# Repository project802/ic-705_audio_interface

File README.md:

# IC-705 Audio Interface

This project was done as a learning exercise for me, and a way to have some fun. I wanted to use my IC-705 with just an iPhone to drive digital mode communications, but limitations of both the radio and the phone meant things like straight USB or Bluetooth wouldn't work. There is a solution path with WiFi-based software or a Digirig, but I didn't want to be locked into a single app (even though I use it on my iPad and find it very good) or buy hardware when I thought I could make something myself and learn.

The result is a minimal solution that is ideal for remote or portable operation (such as POTA or SOTA) with iOS.

All said and done, I have got this working with iFTx and Greyline FT8 to successfully complete QSOs!

In the end, this device is just an audio level shifter with isolation. It can be used with any device (PC, tablet, phone) that has an analog audio input (microphone or line in) and an analog audio output. Just tune the trim pots to hit the voltage levels you need.

Have a PC? Just use the built-in USB functionality or Wi-Fi interface. This adds no value, whatsoever, over those options. This is really for phones using inexpensive (or free) apps that require VOX activation.

## (Non-)Solution Problem Space

### USB Cable or Bluetooth

The radio presents a BT/USB interface to the iOS device, but there are two issues that prevent this from working:
- iOS does not allow for serial port interfaces over USB or BT so an app can't control PTT via the CAT interface. Even with serial port support, this may reduce the number of app choices to ones that specifically support CAT.
- IC-705 doesn't do VOX over USB or BT so we can't just send audio. Icom...come on! The firmware for this is *so tiny*!

There are also reports that the IC-705 has poor RFI rejection via USB so depending on what is plugged in, this could make digital mode operation difficult.

You can theoretically make these interfaces work if you manually activate PTT. That doesn't sound fun.

### Digirig

This is a valid solution. Cost is approximately $45 for a Digirig Lite and I'd estimate $20 (if you can buy individual parts) to make an adapter cable for the IC-705. I still can't confirm if the output levels to the radio are proper, but at least one person has said it functionally works.

https://forum.digirig.net/t/cable-for-icom-ic-705-and-mobile-ft8/10725

### Wi-Fi 

The app SDR-Control does work, but it is sold separately for iPhone and iPad. You would be nearly $100 into software to run on both devices. Its the best solution, objectively, but is costly and locks you into an app. If you change the radio, the app is useless. I happen to like how it works on my iPad, but I've seen some impressive work from other developers in the $2 to $4 range.

## Design Notes

The basis for the design is an [example circuit](images/Icom_example_interface.JPG) that Icom provides in their advanced manual. Addition of a capacitor on the MIC line is required to create a high resistance path to not activate PTT (the IC-705 uses the same pin for both MIC input and PTT).

Design files (PCB, schematic) can be found in the [KiCad directory](KiCad/).

A [screenshot of the schematic](images/ic-705_audio_interface_schematic.JPG) is also available for quick reference.

Icom doesn't seem to publish the MIC input electrical specifications. Through empirical testing, it seems the maximum IC-705 MIC input level before clipping is 50 mVpp.

The methodology was:
1. Set the iPhone volume to max
1. Set the FT8 software to call CQ at ~3000 Hz offset
1. Activate the voice recorder (VOICE TX -> REC/SET -> REC -> T1 -> record)
1. Set MIC gain to 50% (default level)
1. Adjust the trim pot until the meter hits 100%

I landed on AF GAIN = 30 as that seems to be the highest value before output clipping occurs.

Below is the response of the audio interface when stimulated with a signal at the device output and captured at the radio mic input. It is very linear and only drops around 0.5 dB @ 200 Hz, which fits the FT8/4 use case very well. The radio filter(s) will attenuate much more aggressively in the lower sections of the sideband, so look out for loss of power.

## Assembly Notes

This is a straight forward board to assemble. The IC-705 side uses a 3.5mm TRS for the speaker connector and a 2.5mm TRRS for the mic connector. I used a 3.5mm TRRS to connect to the phone side with the jumper soldered, but you can use two cables instead.

For PCB assembly, I recommend doing the SMT parts first, then the trim pots, then the cables.

The output capacitor that goes inline with the IC-705 mic input was left off the PCB to keep the footprint as small as possible. Put one leg into the PCB and the other towards the cable.

[DigiKey BOM](https://www.digikey.com/en/mylists/list/Q781V9DVDD) @ $7

[2.5mm TRRS cable](https://a.co/d/0cmaGAqM) @ $9 ($1.50/ea)

[3.5mm TRRS cable](https://a.co/d/0evUUoQW) @ $8 ($2/ea)

[3.5mm TRS cable](https://a.co/d/0eWTbZUC) @ $8 ($4/ea)

[USB audio interface](https://a.co/d/0cbzTN2W) (others will work, too)

[3D printable case files](https://www.printables.com/model/1877246-ic-705-audio-interface-box)

Below is an image of the cable routing and capacitor placement. It is done this way for strain relief. 

After assembly, tune the trim pots so that the MIC input for the IC-705 reaches 50 mVpp while calling CQ.

I set the device side mic to 45 mVpp as this was saturation for my device. To tune it yourself, use the record function to save a CQ TX to the microSD card, then play it back with AF GAIN = 30. You should get full scale output without clipping and use that to tune the trim pot. Pair with any free app or built-in program that shows the mic level input on your device.

At the time of writing, the total component cost was $14.50 and the PCB was $1.20/ea. I have 8 extra PCBs so create an issue here to contact me about getting one. Send me a self-addressed stamped envelope and I'll send you one for free.

## IC-705 and iOS Settings

IC-705:
- MIC gain = 50% (default)
- COMP = 5 (default)
- VOX gain = 50% (default) but move up if VOX is intermittent
- ANTI VOX = 50% (default)
- Delay = 0.0s
- Voice delay = OFF (default)
- VOX = on
- AF GAIN = 30
- Frequency = as appropriate (14.074, etc) 
- Mode = USB (do NOT use USB-D, VOX doesn't work)

iOS:
- Put the phone to silent mode. ALL sounds will make its way to the radio, so silent mode enabled to prevent your TX from getting in trouble when you get a notification.
- Turn the volume all the way up (which should have been where it was when you tuned the trim pots).

## Application Specific Settings and Build Notes

iFTx:
- Seems to work well out of the box

Greyline FT8
- Set the "Drive" slider to -1 dB before tuning the hardware interface gain. I have a theory that iOS is doing funky things with full scale signals (regardless of volume slider position) that even just -1 dB has been shown to lower THD by half and the noise floor on the transmitted signal by 20 dB. 
- Make sure you take the audio signal from the left channel. 1.6 and newer have mono audio data and the right channel is optionally fed with a tone for PTT/VOX circuits.

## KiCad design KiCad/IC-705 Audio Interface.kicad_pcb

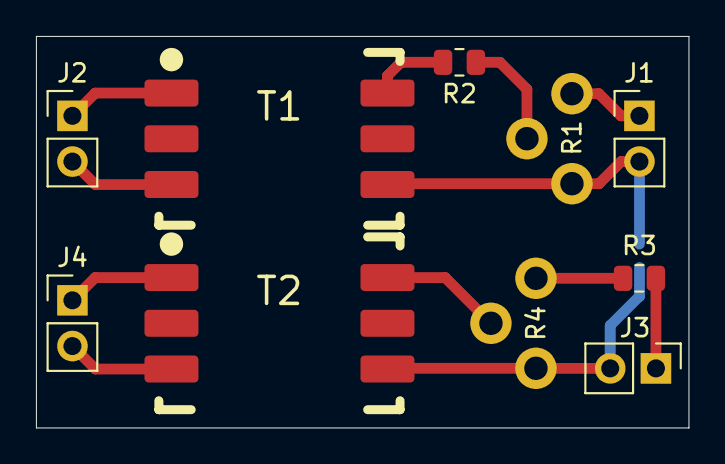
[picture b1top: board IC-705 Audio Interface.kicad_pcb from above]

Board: 2 copper layers, 36.2 x 21.8 mm, 11 parts (1 on the bottom side), 12 nets.

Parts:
J1, J2, J3, J4: Conn_01x02; PinHeader_1x02_P2.54mm_Vertical
JP1: SolderJumper_2_Open; SolderJumper-2_P1.3mm_Open_RoundedPad1.0x1.5mm
R1, R4: H2.5
R2, R3: 10k; R_0805_2012Metric
T1, T2: SM-LP-5001

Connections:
/705_MIC: J4.1, T2.1
/705_MIC_SH: J4.2, T2.3
/705_SP: J2.1, T1.1
/705_SP_SH: J2.2, T1.3
/COMP_MIC: J1.1, R1.1
/COMP_MIC_SH: J1.2, JP1.1 (A), R1.3, T1.4
/COMP_SP: J3.1, R3.2
/COMP_SP_SH: J3.2, JP1.2 (B), R4.3, T2.4
unnamed: R1.2, R2.2
unnamed: R2.1, T1.6
unnamed: R3.1, R4.1
unnamed: R4.2, T2.6
